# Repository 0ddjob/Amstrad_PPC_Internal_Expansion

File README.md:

# Amstrad_PPC_XT_CF_Lite
Internal CF interface for the Amstrad PPC512/640

Replaces the internal modem board with a combination ISA interface & XT-IDE/Compact Flash interface.<br> 

Heavily based on Sergey Kiselev's design<br>
[Github page](https://github.com/skiselev)<br>
[WWW page](http://www.malinov.com/Home/sergeys-projects/xt-cf-lite)<br>

Which is apparently a remake of James Pearce's card:<br>
[WWW page](http://www.lo-tech.co.uk/wiki/XT-CF-lite)<br>

I am using some of Sergey's Kicad symbols/footprints:<br>
[Sergey's Kicad symbols](https://github.com/skiselev/my_kicad_library)<br>

Changes requires for internal mounting in the Amstrad PPC:<br>
[1] The following signals are generated directly from the internal gate arrays and should be buffered with a non-inverting buffer (i.e. 72HC244): A00 to A07, !MEMW, !MEMR, !IOW, !IOR, RESET<br>
_(there are others but irrelevant for our purposes)_<br>
[2] The data signals (D0 to D7) are at CMOS levels and should be pulled up to TTL levels with 10KΩ resistors<br>
[3] The internal modem board we are replacing is roughly 200x120mm<br>
[4] Technically the PPC should be powered by the "expansion unit" and not the other way around ... don't tell anyone<br>

Currently untested ...<br><br>

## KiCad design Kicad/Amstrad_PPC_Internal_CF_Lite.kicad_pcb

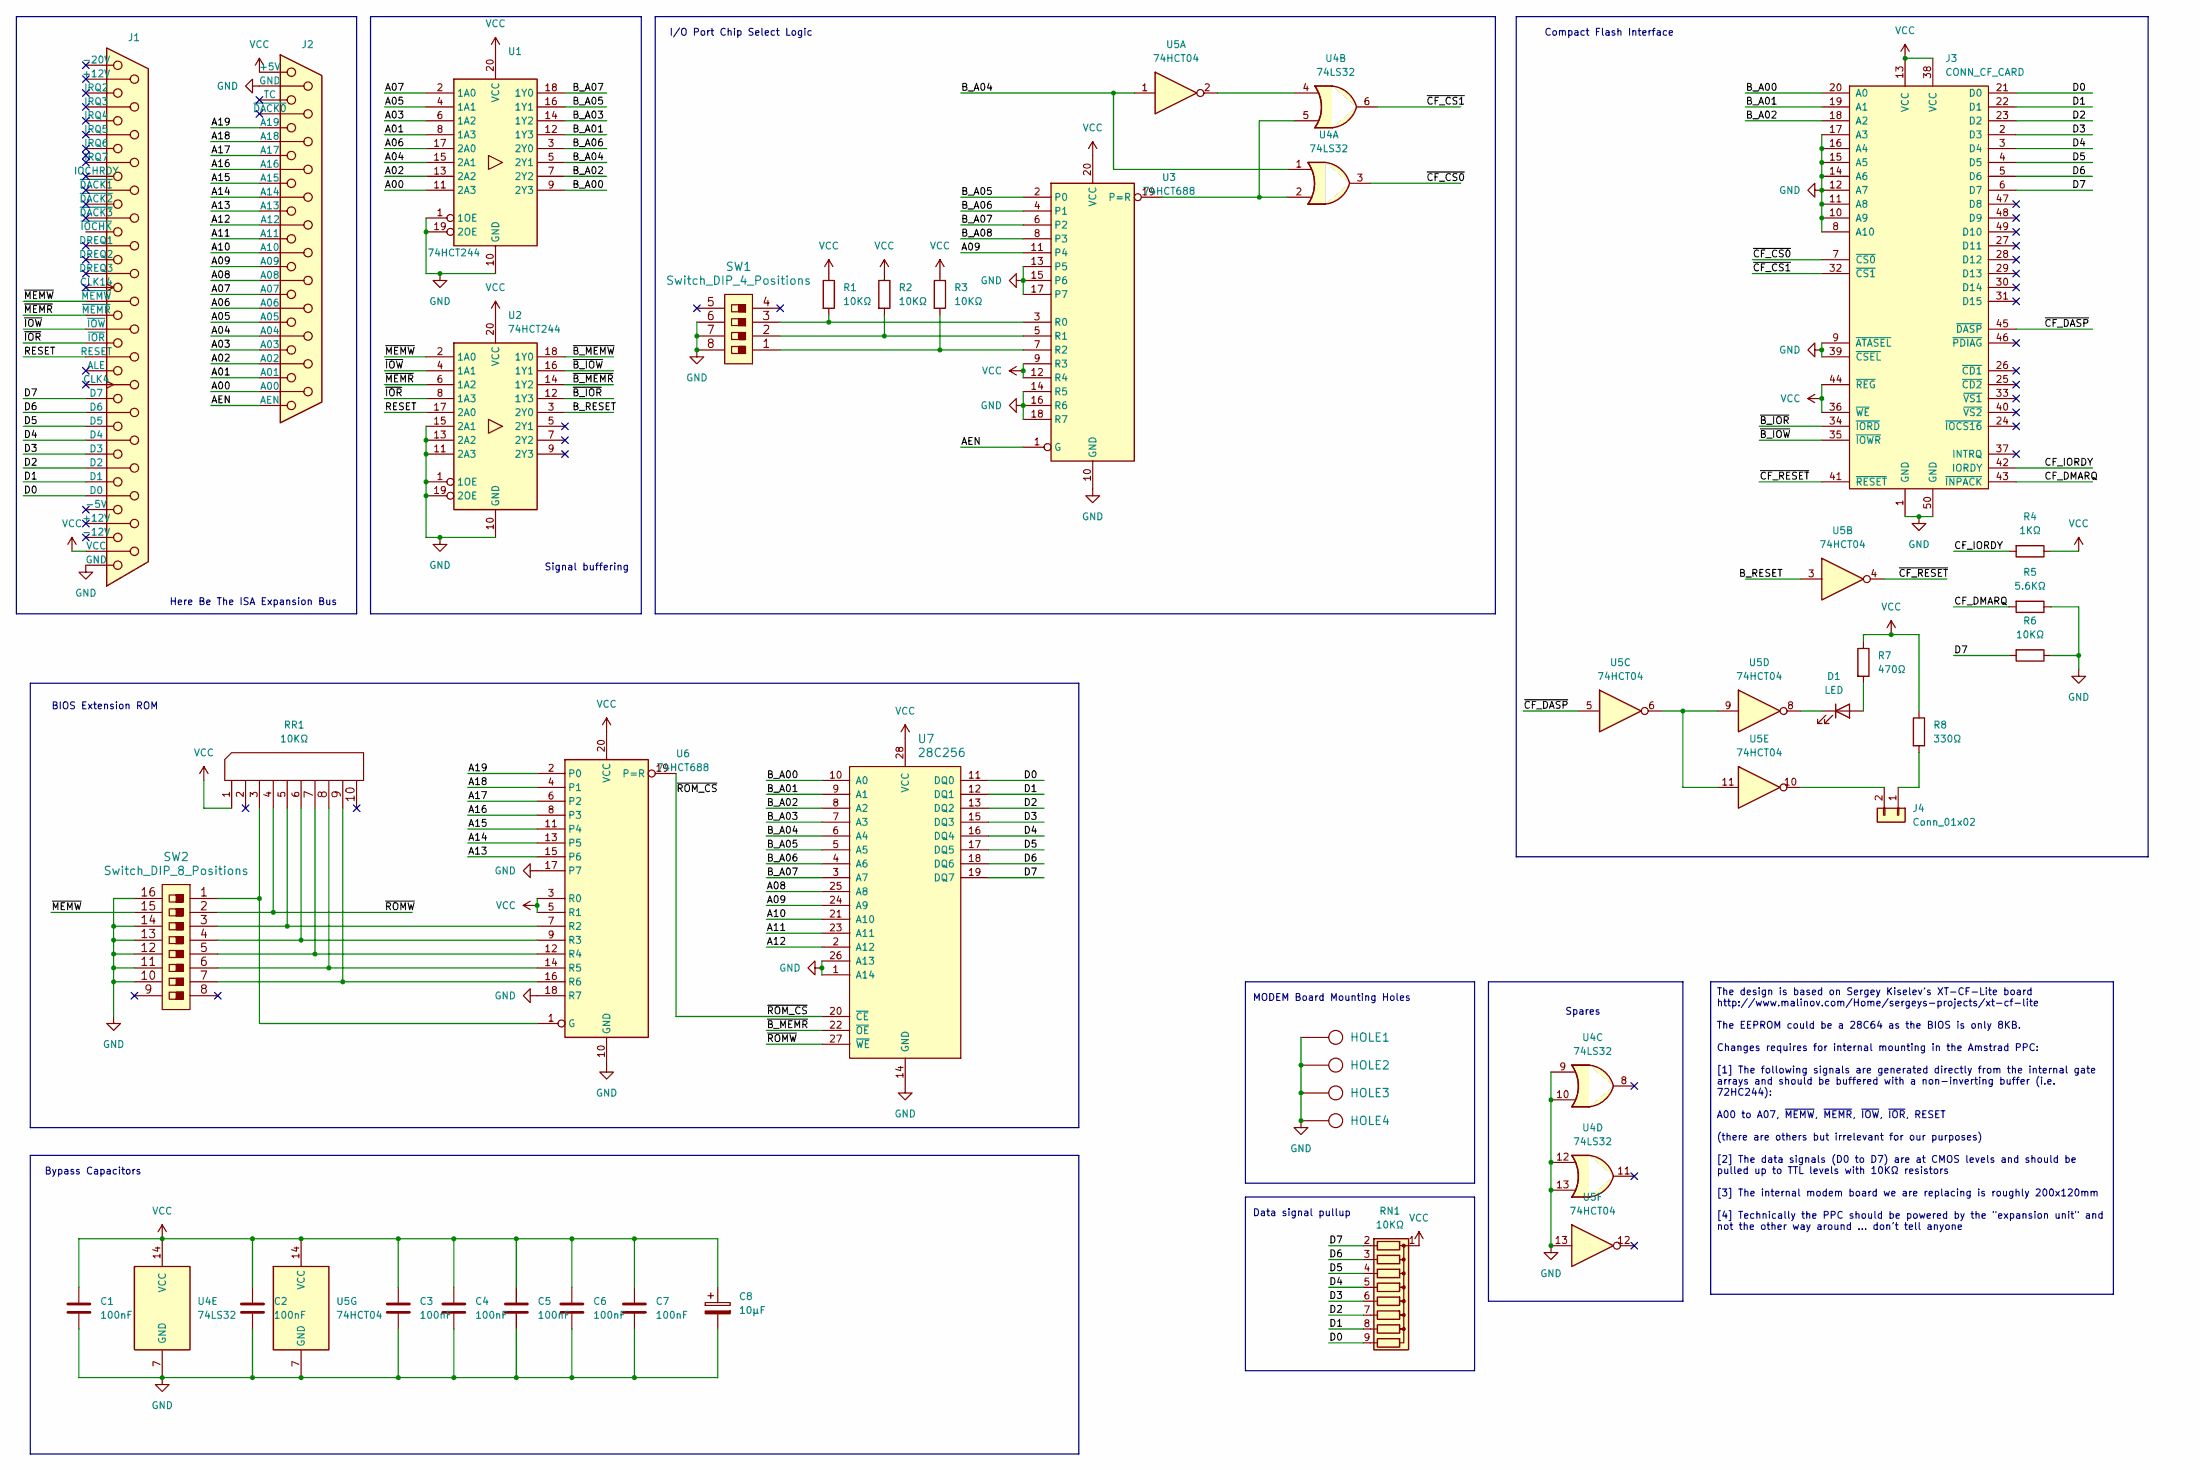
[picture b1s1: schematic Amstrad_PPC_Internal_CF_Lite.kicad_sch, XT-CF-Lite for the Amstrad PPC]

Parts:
C1, C2, C3, C4, C5, C6, C7: 100nF; C_Disc_D4.7mm_W2.5mm_P5.00mm
C8: 10µF; C_Radial_D4.0mm_H5.0mm_P1.50mm
D1: LED; PinHeader_1x02_P2.54mm_Vertical
HOLE1, HOLE2, HOLE3, HOLE4: HOLE; Hole_3mm
J1: Amstrad_PPC_ISA_Connector_B; DSUB-37_Female_EdgeMount_P2.77mm
J2: Amstrad_PPC_ISA_Connector_A; DSUB-25_Female_EdgeMount_P2.77mm
J3: CONN_CF_CARD; Conn_CF_N7E50-Q516XX-40
J4: Conn_01x02; PinHeader_1x02_P2.54mm_Vertical
R1, R2, R3, R6: 10KΩ; R_Axial_DIN0207_L6.3mm_D2.5mm_P7.62mm_Horizontal
R4: 1KΩ; R_Axial_DIN0207_L6.3mm_D2.5mm_P7.62mm_Horizontal
R5: 5.6KΩ; R_Axial_DIN0207_L6.3mm_D2.5mm_P7.62mm_Horizontal
R7: 470Ω; R_Axial_DIN0207_L6.3mm_D2.5mm_P7.62mm_Horizontal
R8: 330Ω; R_Axial_DIN0207_L6.3mm_D2.5mm_P7.62mm_Horizontal
RN1: 10KΩ; R_Array_SIP9
RR1: 10KΩ; R_Array_SIP10
SW1: Switch_DIP_4_Positions
SW2: Switch_DIP_8_Positions
U1, U2: 74HCT244; DIP-20_W7.62mm
U3, U6: 74HCT688; DIP-20_W7.62mm
U4: 74LS32; DIP-14_W7.62mm
U5: 74HCT04; DIP-14_W7.62mm
U7: 28C256; DIP-28_W15.24mm

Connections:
/A00: J2.25 (A00), U1.11 (2A3)
/A01: J2.12 (A01), U1.8 (1A3)
/A02: J2.24 (A02), U1.13 (2A2)
/A03: J2.11 (A03), U1.6 (1A2)
/A04: J2.23 (A04), U1.15 (2A1)
/A05: J2.10 (A05), U1.4 (1A1)
/A06: J2.22 (A06), U1.17 (2A0)
/A07: J2.9 (A07), U1.2 (1A0)
/A08: J2.21 (A08), U7.25 (A8)
/A09: J2.8 (A09), U3.11 (P4), U7.24 (A9)
/A10: J2.20 (A10), U7.21 (A10)
/A11: J2.7 (A11), U7.23 (A11)
/A12: J2.19 (A12), U7.2 (A12)
/A13: J2.6 (A13), U6.15 (P6)
/A14: J2.18 (A14), U6.13 (P5)
/A15: J2.5 (A15), U6.11 (P4)
/A16: J2.17 (A16), U6.8 (P3)
/A17: J2.4 (A17), U6.6 (P2)
/A18: J2.16 (A18), U6.4 (P1)
/A19: J2.3 (A19), U6.2 (P0)
/AEN: J2.13 (AEN), U3.1 (G)
/B_A00: J3.20 (A0), U1.9 (2Y3), U7.10 (A0)
/B_A01: J3.19 (A1), U1.12 (1Y3), U7.9 (A1)
/B_A02: J3.18 (A2), U1.7 (2Y2), U7.8 (A2)
/B_A03: U1.14 (1Y2), U7.7 (A3)
/B_A04: U1.5 (2Y1), U4.1, U5.1, U7.6 (A4)
/B_A05: U1.16 (1Y1), U3.2 (P0), U7.5 (A5)
/B_A06: U1.3 (2Y0), U3.4 (P1), U7.4 (A6)
/B_A07: U1.18 (1Y0), U3.6 (P2), U7.3 (A7)
/B_A08: U3.8 (P3)
/B_RESET: U2.3 (2Y0)
/CF_DMARQ: J3.43 (~INPACK), R5.2
/CF_IORDY: J3.42 (IORDY), R4.2
/D0: J1.35 (D0), J3.21 (D0), RN1.9 (R8), U7.11 (DQ0)
/D1: J1.16 (D1), J3.22 (D1), RN1.8 (R7), U7.12 (DQ1)
/D2: J1.34 (D2), J3.23 (D2), RN1.7 (R6), U7.13 (DQ2)
/D3: J1.15 (D3), J3.2 (D3), RN1.6 (R5), U7.15 (DQ3)
/D4: J1.33 (D4), J3.3 (D4), RN1.5 (R4), U7.16 (DQ4)
/D5: J1.14 (D5), J3.4 (D5), RN1.4 (R3), U7.17 (DQ5)
/D6: J1.32 (D6), J3.5 (D6), RN1.3 (R2), U7.18 (DQ6)
/D7: J1.13 (D7), J3.6 (D7), R6.2, RN1.2 (R1), U7.19 (DQ7)
/RESET: J1.30 (RESET), U2.17 (2A0)
/~B_IOR: J3.34 (~IORD), U2.12 (1Y3)
/~B_IOW: J3.35 (~IOWR), U2.16 (1Y1)
/~B_MEMR: U2.14 (1Y2), U7.22 (~OE)
/~B_MEMW: U2.18 (1Y0)
/~CF_CS0: J3.7 (~CS0), U4.3
/~CF_CS1: J3.32 (~CS1), U4.6
/~CF_DASP: J3.45 (~DASP), U5.5
/~CF_RESET: J3.41 (~RESET), U5.4
/~IOR: J1.11 (~IOR), U2.8 (1A3)
/~IOW: J1.29 (~IOW), U2.4 (1A1)
/~MEMR: J1.10 (~MEMR), U2.6 (1A2)
/~MEMW: J1.28 (~MEMW), SW2.15, U2.2 (1A0)
/~ROMW: RR1.4, SW2.2, U7.27 (~WE)
/~ROM_CS: U6.19 (P=R), U7.20 (~CE)
GND: C1.2, C2.2, C3.2, C4.2, C5.2, C6.2, C7.2, C8.2, HOLE1.1, HOLE2.1, HOLE3.1, HOLE4.1, J1.19 (GND), J2.14 (GND), J3.1 (GND), J3.8 (A10), J3.9 (~ATASEL), J3.10 (A9), J3.11 (A8), J3.12 (A7), J3.14 (A6), J3.15 (A5), J3.16 (A4), J3.17 (A3), J3.39 (~CSEL), J3.50 (GND), R5.1, R6.1, SW1.6, SW1.7, SW1.8, SW2.10, SW2.11, SW2.12, SW2.13, SW2.14, SW2.16, U1.1 (1OE), U1.10 (GND), U1.19 (2OE), U2.1 (1OE), U2.10 (GND), U2.11 (2A3), U2.13 (2A2), U2.15 (2A1), U2.19 (2OE), U3.10 (GND), U3.13 (P5), U3.14 (R5), U3.15 (P6), U3.16 (R6), U3.17 (P7), U3.18 (R7), U4.7 (GND), U4.9, U4.10, U4.12, U4.13, U5.7 (GND), U5.13, U6.10 (GND), U6.17 (P7), U6.18 (R7), U7.1 (A14), U7.14 (GND), U7.26 (A13)
unnamed: D1.2 (A), R7.2
unnamed: D1.1 (K), U5.8
unnamed: J4.1, R8.2
unnamed: J4.2, U5.10
unnamed: U3.19 (P=R), U4.2, U4.5
unnamed: R1.2, SW1.3, U3.3 (R0)
unnamed: R2.2, SW1.2, U3.5 (R1)
unnamed: R3.2, SW1.1, U3.7 (R2)
unnamed: U4.4, U5.2
unnamed: U5.6, U5.9, U5.11
unnamed: RR1.3, SW2.1, U6.1 (G)
unnamed: RR1.5, SW2.3, U6.7 (R2)
unnamed: RR1.6, SW2.4, U6.9 (R3)
unnamed: RR1.7, SW2.5, U6.12 (R4)
unnamed: RR1.8, SW2.6, U6.14 (R5)
unnamed: RR1.9, SW2.7, U6.16 (R6)
VCC: C1.1, C2.1, C3.1, C4.1, C5.1, C6.1, C7.1, C8.1, J1.37 (VCC), J2.1 (+5V), J3.13 (VCC), J3.36 (~WE), J3.38 (VCC), J3.44 (~REG), R1.1, R2.1, R3.1, R4.1, R7.1, R8.1, RN1.1 (common), RR1.1 (COM), U1.20 (VCC), U2.20 (VCC), U3.9 (R3), U3.12 (R4), U3.20 (VCC), U4.14 (VCC), U5.14 (VCC), U6.3 (R0), U6.5 (R1), U6.20 (VCC), U7.28 (VCC)

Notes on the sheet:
The design is based on Sergey Kiselev's XT-CF-Lite board http://www.malinov.com/Home/sergeys-projects/xt-cf-lite The EEPROM could be a 28C64 as the BIOS is only 8KB. Changes requires for internal mounting in the Amstrad PPC: [1] The following signals are generated directly from the internal gate ar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
Signal buffering
Spares
Compact Flash Interface
I/O Port Chip Select Logic
BIOS Extension ROM
Data signal pullup
MODEM Board Mounting Holes
Here Be The ISA Expansion Bus
Bypass Capacitors

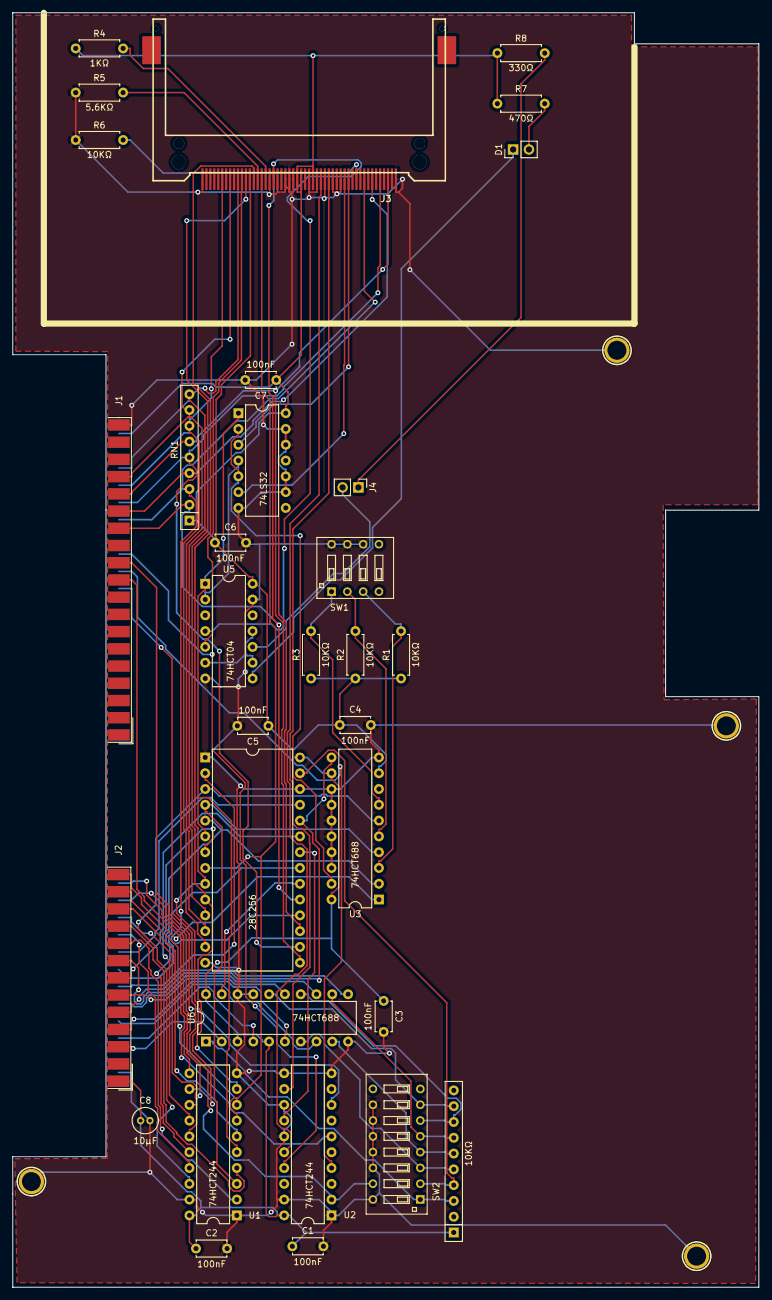
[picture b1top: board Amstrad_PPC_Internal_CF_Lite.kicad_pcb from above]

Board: 2 copper layers, 120.0 x 205.0 mm, 36 parts (0 on the bottom side), 71 nets.

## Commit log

2023-08-24 Initial description
2023-08-24 Added image
2023-08-24 Initial/untested set of Kicad 7 files
    It ain't pretty ... and it ain't tested ... this is my first project using Kicad so it'll be a bit rough still ...
2023-08-24 Added note about Sergey's Kicad symbol library
2023-08-24 Notes about Amstrad PPC requirements
2023-09-07 Renaming
2023-09-07 Refinements to PCB
2023-09-07 Added PCB image
2023-09-07 Added internal modem photo
